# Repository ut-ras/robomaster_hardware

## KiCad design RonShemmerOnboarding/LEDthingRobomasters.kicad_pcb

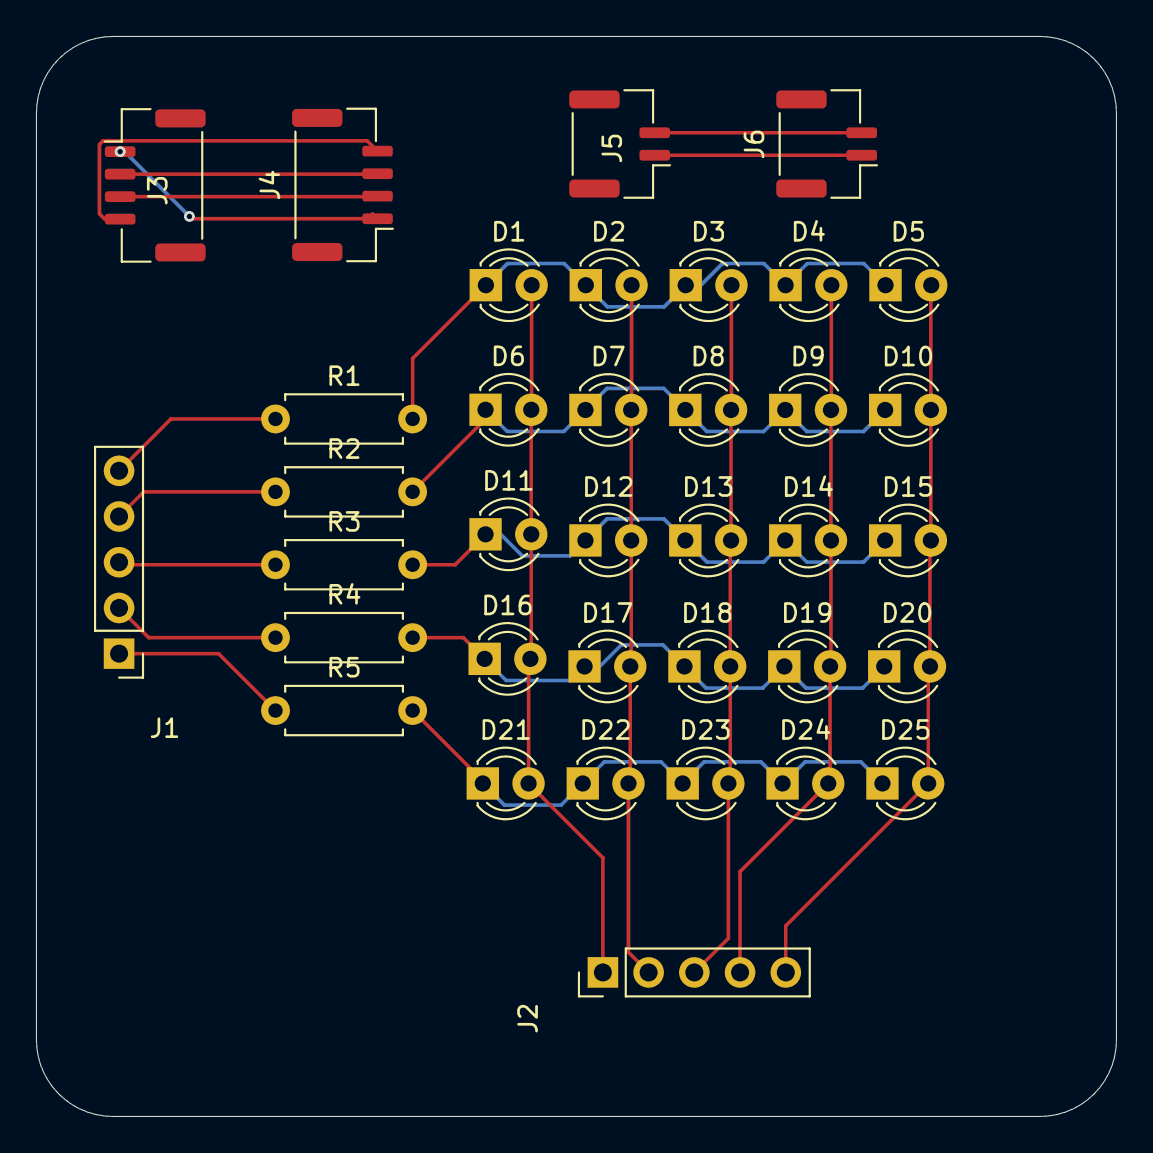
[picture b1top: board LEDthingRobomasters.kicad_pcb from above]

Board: 2 copper layers, 60.0 x 60.0 mm, 36 parts (0 on the bottom side), 21 nets.

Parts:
D1, D2, D3, D4, D5, D6, D7, D8, D9, D10, D11, D12, D13, D14, D15, D16, D17, D18, D19, D20, D21, D22, D23, D24, D25: LED; LED_D3.0mm
J1, J2: Conn_01x05; PinHeader_1x05_P2.54mm_Vertical
J3, J4: Conn_01x04; JST_GH_BM04B-GHS-TBT_1x04-1MP_P1.25mm_Vertical
J5, J6: Conn_01x02; JST_GH_BM02B-GHS-TBT_1x02-1MP_P1.25mm_Vertical
R1, R2, R3, R4, R5: R_US; R_Axial_DIN0207_L6.3mm_D2.5mm_P7.62mm_Horizontal

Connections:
+3V3: J3.1, J4.1
/CAN_H: J5.1, J6.1
/CAN_L: J5.2, J6.2
/RX: J3.3, J4.2
/TX: J3.2, J4.3
GND: J3.4, J4.4
unnamed: D1.2 (A), D6.2 (A), D11.2 (A), D16.2 (A), D21.2 (A), J2.1
unnamed: D1.1 (K), D2.1 (K), D3.1 (K), D4.1 (K), D5.1 (K), R1.2
unnamed: D5.2 (A), D10.2 (A), D15.2 (A), D20.2 (A), D25.2 (A), J2.5
unnamed: D6.1 (K), D7.1 (K), D8.1 (K), D9.1 (K), D10.1 (K), R2.2
unnamed: D11.1 (K), D12.1 (K), D13.1 (K), D14.1 (K), D15.1 (K), R3.2
unnamed: D2.2 (A), D7.2 (A), D12.2 (A), D17.2 (A), D22.2 (A), J2.2
unnamed: D3.2 (A), D8.2 (A), D13.2 (A), D18.2 (A), D23.2 (A), J2.3
unnamed: D4.2 (A), D9.2 (A), D14.2 (A), D19.2 (A), D24.2 (A), J2.4
unnamed: D16.1 (K), D17.1 (K), D18.1 (K), D19.1 (K), D20.1 (K), R4.2
unnamed: D21.1 (K), D22.1 (K), D23.1 (K), D24.1 (K), D25.1 (K), R5.2
unnamed: J1.1, R5.1
unnamed: J1.2, R4.1
unnamed: J1.3, R3.1
unnamed: J1.4, R2.1
unnamed: J1.5, R1.1

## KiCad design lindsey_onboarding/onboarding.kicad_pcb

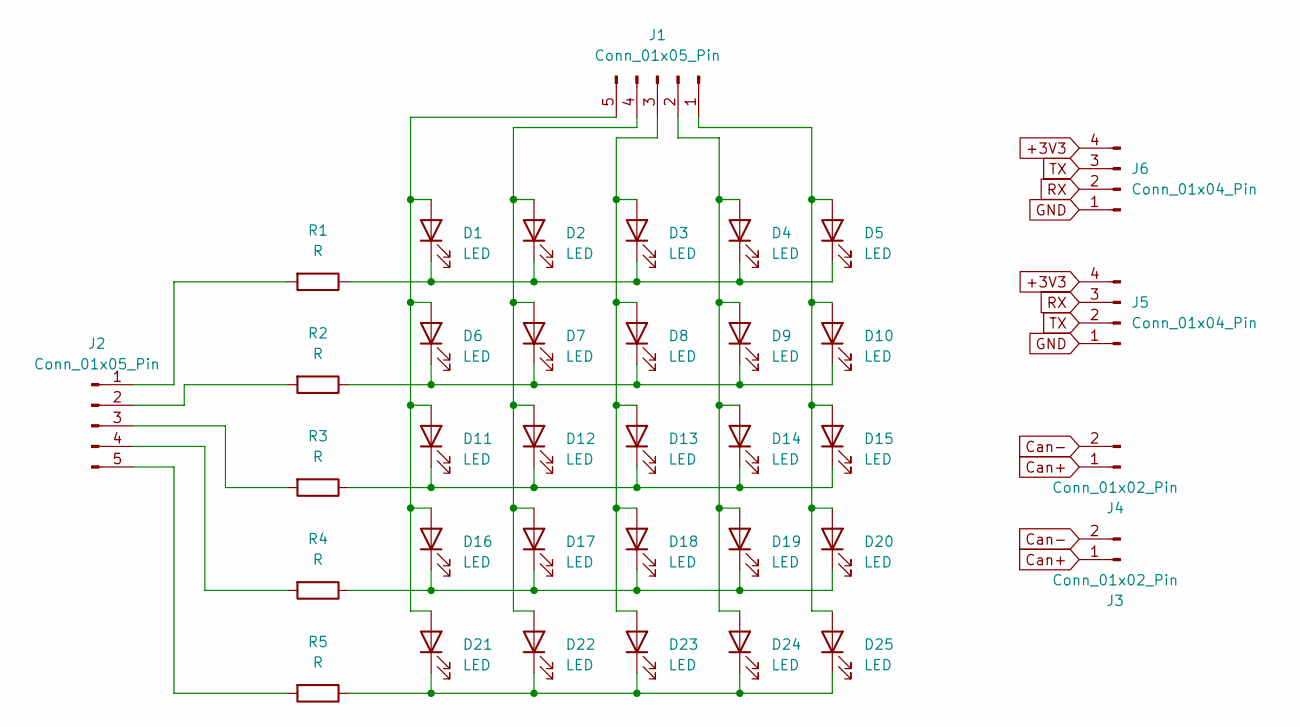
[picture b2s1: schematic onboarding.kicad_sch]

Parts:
D1, D2, D3, D4, D5, D6, D7, D8, D9, D10, D11, D12, D13, D14, D15, D16, D17, D18, D19, D20, D21, D22, D23, D24, D25: LED; LED_D3.0mm
J1, J2: Conn_01x05_Pin; Harwin_M20-89005xx_1x05_P2.54mm_Horizontal
J3, J4: Conn_01x02_Pin; PinHeader_1x02_P2.54mm_Horizontal
J5, J6: Conn_01x04_Pin; PinHeader_1x04_P2.54mm_Horizontal
R1, R2, R3, R4, R5: R; R_Axial_DIN0207_L6.3mm_D2.5mm_P7.62mm_Horizontal

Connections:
+3V3: J5.4, J6.4
Can+: J3.1, J4.1
Can-: J3.2, J4.2
GND: J5.1, J6.1
unnamed: D1.2 (A), D6.2 (A), D11.2 (A), D16.2 (A), D21.2 (A), J1.5
unnamed: D1.1 (K), D2.1 (K), D3.1 (K), D4.1 (K), D5.1 (K), R1.1
unnamed: D5.2 (A), D10.2 (A), D15.2 (A), D20.2 (A), D25.2 (A), J1.1
unnamed: D6.1 (K), D7.1 (K), D8.1 (K), D9.1 (K), D10.1 (K), R2.1
unnamed: D11.1 (K), D12.1 (K), D13.1 (K), D14.1 (K), D15.1 (K), R3.1
unnamed: D2.2 (A), D7.2 (A), D12.2 (A), D17.2 (A), D22.2 (A), J1.4
unnamed: D3.2 (A), D8.2 (A), D13.2 (A), D18.2 (A), D23.2 (A), J1.3
unnamed: D4.2 (A), D9.2 (A), D14.2 (A), D19.2 (A), D24.2 (A), J1.2
unnamed: D16.1 (K), D17.1 (K), D18.1 (K), D19.1 (K), D20.1 (K), R4.1
unnamed: D21.1 (K), D22.1 (K), D23.1 (K), D24.1 (K), D25.1 (K), R5.1
unnamed: J2.1, R1.2
unnamed: J2.2, R2.2
unnamed: J2.3, R3.2
unnamed: J2.4, R4.2
unnamed: J2.5, R5.2
RX: J5.3, J6.2
TX: J5.2, J6.3

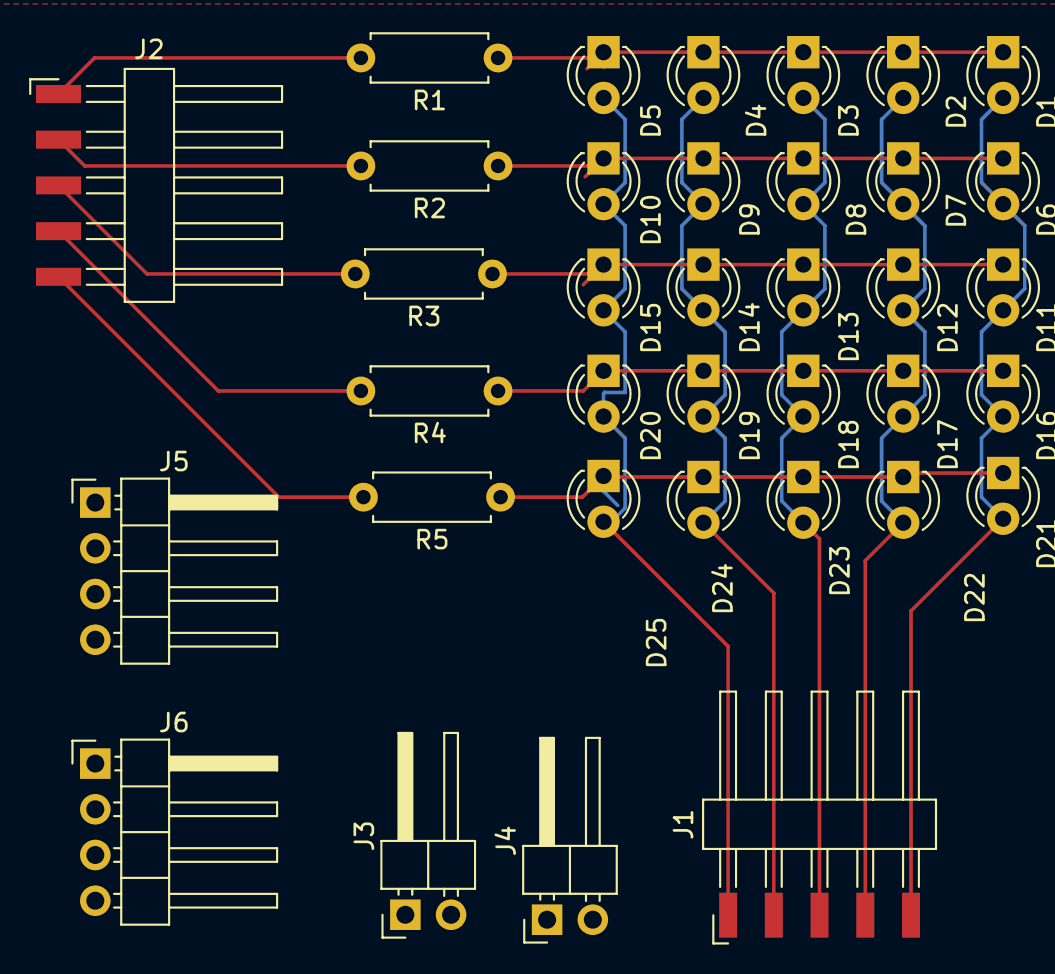
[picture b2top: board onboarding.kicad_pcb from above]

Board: 2 copper layers, 36 parts (0 on the bottom side), 21 nets.
